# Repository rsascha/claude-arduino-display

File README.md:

# CrowPanel ESP32 5.79" E-Paper HMI Display

Setup für das Elecrow CrowPanel ESP32 5.79" E-Paper HMI Display (272×792, S/W, SPI).

## Hardware

| | |
|---|---|
| MCU | ESP32-S3-WROOM-1-N8R8 (8 MB Flash, 8 MB OPI-PSRAM, 240 MHz) |
| Display | 5.79", 272×792, Schwarz/Weiß |
| Display-Controller | 2× SSD1683 (zwei Panel-Hälften) |
| USB-UART | CH340 (VID 0x1A86 / PID 0x7523) |
| Port | `/dev/cu.usbserial-210` |
| Akku-Anschluss | SH1.0, 2-polig (1,0 mm Raster), 3,7 V Li-Ion, Ladeschaltung an Bord |

**Der BAT-Stecker ist SH1.0, nicht 1,25 mm.** Ein JST/MX1.25-Akku passt nicht ohne
Adapter. Und: Handelsübliche SH1.0-Akkukabel haben teils vertauschte Polung — vor dem
ersten Anstecken gegen den Aufdruck + / − am Stecker messen. Belege und Quellen in
`material/CLAUDE.md` → *Akkuanschluss*; das Benutzerhandbuch schreibt an der Stelle
nur „BAT" und nennt den Typ nicht.

## Board-Einstellungen (Arduino IDE)

`Werkzeuge` →

| Einstellung | Wert |
|---|---|
| Board | **ESP32S3 Dev Module** |
| Flash Size | **8MB (64Mb)** |
| Partition Scheme | **Huge APP (3MB No OTA/1MB SPIFFS)** |
| PSRAM | **OPI PSRAM** |
| CPU Frequency | 240MHz (WiFi) |
| Flash Mode | QIO 80MHz |
| USB CDC On Boot | Disabled |
| Upload Mode | UART0 / Hardware CDC |
| Upload Speed | **460800** — 921600 scheitert beim CH340 mit "Unable to verify flash chip connection" |
| Port | `/dev/cu.usbserial-210` |

Als FQBN für die CLI:

```
esp32:esp32:esp32s3:FlashSize=8M,PartitionScheme=huge_app,PSRAM=opi,CPUFreq=240,FlashMode=qio,UploadSpeed=460800
```

## Pinbelegung E-Paper

Maßgeblich ist `spi.h` in den Beispielen — **nicht** `DEV_Config.h` aus der `EPD`-Library
(die enthält die Waveshare-Standardpins und passt nicht zu diesem Board).

| Signal | GPIO |
|---|---|
| SCK | 12 |
| MOSI | 11 |
| RES (Reset) | 47 |
| DC | 46 |
| CS | 45 |
| BUSY | 48 |
| Display-Power-Enable | 7 (muss in `setup()` auf HIGH!) |

Ohne `digitalWrite(7, HIGH)` bleibt das Panel stromlos und zeigt nichts an.

## Bedienelemente

Laut Benutzerhandbuch (`material/crowpanel-5.79-benutzerhandbuch.pdf`, S. 2–3) hat das
Board fünf Bedienelemente. Drei davon sitzen an der Gehäusekante und sind frei
programmierbar, zwei liegen auf der Platine und sind fest verdrahtet:

| Element | Lage | Funktion |
|---|---|---|
| MENU | Kante | frei programmierbar |
| Rotary Switch (Drehschalter) | Kante | frei programmierbar, dreh- **und** drückbar |
| EXIT | Kante | frei programmierbar |
| BOOT | Platine | hält GPIO 0 auf LOW → Flash-Modus |
| RESET | Platine | zieht EN auf LOW → Neustart |

Das Handbuch nennt keine GPIOs. Sie stehen in `examples/5.79_key`; die Zuordnung wurde
am 23.08.2026 **am Gerät verifiziert** — jedes Element einzeln betätigt und der Zähler
auf dem Panel abgelesen. Die Positionsangaben gelten für die Ausrichtung **Querformat,
USB-Anschluss oben, Bedienelemente an der linken Kante**:

| Position | Element | GPIO | `#define` in `5.79_key` |
|---|---|---|---|
| oben | EXIT | 1 | `EXIT_KEY` |
| Mitte, Rad nach oben | Drehschalter | 4 | `NEXT_KEY` |
| Mitte, Rad drücken | Drehschalter | 5 | `OK_KEY` |
| Mitte, Rad nach unten | Drehschalter | 6 | `PRV_KEY` |
| unten | MENU | 2 | `HOME_KEY` |

Die Reihenfolge an der Kante ist damit **EXIT – Drehschalter – MENU**. Das Handbuch (S. 2)
zeigt sie umgekehrt, weil seine Abbildung die **Rückseite** mit USB-C unten darstellt —
gedreht auf die obige Ausrichtung kehrt sich die Reihenfolge um.

Nachvollziehen lässt sich das mit `make flash SKETCH=examples/5.79_key`: Jeder Tastendruck
schreibt seinen Namen auf Display und Konsole. Zwei Dinge sind an der Elecrow-Vorlage
angepasst — ein Textrest `Reset Tag` mitten im Code, der das Kompilieren verhinderte,
und `Paint_NewImage(..., 0, ...)` statt `Rotation` (180), damit das Bild bei USB oben
richtig herum steht.

Die Taster liegen gegen Masse und werden mit `pinMode(pin, INPUT)` gelesen;
gedrückt ist **LOW**. GPIO 41 schaltet die Power-LED (`examples/5.79_PWR`).

## Verwendung

```bash
make build                              # Standard-Sketch kompilieren
make flash                              # kompilieren + flashen
make monitor                            # serieller Monitor (115200)
make port                               # erkannten Port anzeigen

make flash SKETCH=examples/5.79_wifi    # anderen Sketch wählen
```

## Struktur

```
sketches/         Eigene Sketches — siehe Abschnitt „Sketches"
libraries/        Elecrow-Libraries — zugleich Sketchbook-libraries/
examples/         Offizielle Elecrow-Beispiele + Demos
factory_firmware/ Werksfirmware als Backup
material/         Handbuch + Datenblätter (PDF und .txt), Fotos des laufenden Panels,
                  Kommando- und GPIO-Tabellen als YAML
tools/simulator/  Host-Build eines Sketches -> PNG, ohne Gerät
Makefile          Build-/Flash-Targets, dazu `make sim` und `make material-txt`
LICENSE           MIT für den eigenen Code, plus Herkunft des Fremdmaterials
```

Ein Sketch-Ordner und die `.ino` darin müssen **gleich heißen**
(`sketches/hello_epaper/hello_epaper.ino`). Alle weiteren Dateien im Ordner
werden automatisch mitkompiliert — deshalb liegen `EPD.cpp`, `spi.cpp` &
Co. direkt neben der `.ino` und nicht in `libraries/`.

`src/` wäre als Ordnername ungeeignet: Arduino behandelt ein `src/`
*innerhalb* eines Sketches als Sonderfall (wird als einziger Unterordner
rekursiv kompiliert). Im Sketchbook-Wurzelverzeichnis sind zudem
`libraries/` und `hardware/` fest vergeben.

Der Sketchbook-Pfad von Arduino IDE **und** arduino-cli zeigt auf dieses
Verzeichnis, damit `libraries/`, `examples/` und `sketches/` automatisch gefunden werden.
Rückgängig: in der IDE unter `Einstellungen → Sketchbook-Speicherort`, für die CLI
mit `arduino-cli config set directories.user ~/Documents/Arduino`.

## Sketches

Eigene Sketches in `sketches/`. Kompilieren und flashen mit
`make flash SKETCH=sketches/<name>`.

| Sketch | Kurz | WLAN |
|---|---|---|
| [`hello_epaper`](sketches/hello_epaper) | Text, Formen, Grundlayout — der Einstieg | – |
| [`smiley`](sketches/smiley) | eigene Bogen-Funktion, `safePixel()`, Kreise mit Strichstärke | – |
| [`ha_temperatur`](sketches/ha_temperatur) | ein Sensorwert aus Home Assistant, groß auf dem Display | ja |
| [`ha_verlauf`](sketches/ha_verlauf) | Temperaturkurve über 10 Tage mit Gitter und Achsen | ja |
| [`ha_raeume`](sketches/ha_raeume) | sechs Räume plus Außen in einem Diagramm | ja |
| [`ha_kacheln`](sketches/ha_kacheln) | alle Räume plus Außen als Kacheln, sortiert nach Temperatur | ja |
| [`ha_wetter`](sketches/ha_wetter) | Wind, Luftdruck und Wetterlage in vier Spalten | ja |
| [`ha_wechsel`](sketches/ha_wechsel) | Temperaturen und Wetter im Wechsel, EXIT und MENU bedienbar | ja |
| [`ha_umschalten`](sketches/ha_umschalten) | zwei Sensoren im Wechsel; Testsketch für die Refresh-Modi | ja |
| [`progress_bar`](sketches/progress_bar) | Fortschrittsanzeige, EXIT startet neu — Partial-Refresh | – |
| [`bedienleiste`](sketches/bedienleiste) | Laschen für die drei Bedienelemente, daneben vier umschaltbare Seiten | – |

**`hello_epaper`** — der Startpunkt. Text in mehreren Größen, ein Rahmen, ein paar Formen.
Zeigt, warum der Puffer 27200 Byte groß ist und was `digitalWrite(7, HIGH)` damit zu tun
hat, dass überhaupt etwas erscheint.

**`smiley`** — ergänzt fehlende Zeichenprimitive. `EPD.h` kann Linie, Rechteck und Kreis,
aber **keinen Bogen**; der Mund wird deshalb aus einzelnen Pixeln gebaut (Schrittweite
`0.5f / radius`, sonst reißt die Linie bei großen Radien auf). Hier steht auch der
`safePixel()`-Wrapper, den jeder eigene Zeichencode braucht: `Paint_SetPixel()` prüft seine
Koordinaten nicht und schreibt sonst über den Puffer hinaus.

**`ha_temperatur`** — ein Wert aus Home Assistant über `GET /api/states/<entity_id>`, groß
dargestellt. Fehler landen **auf dem Display**, nicht nur im Log: HTTP 401 und 404 werden
mit einem Hinweis auf die wahrscheinliche Ursache angezeigt, sonst sieht man bei einem
Problem nur ein leeres Panel.

**`ha_verlauf`** — Aktualisierung alle 30 Minuten.
Holt 10 Tage History und zeichnet daraus eine Kurve mit Gitter, Datums- und Gradachse. Die
Antwort (~19 KB) wird direkt mit `strstr()` gescannt statt mit einem JSON-Parser, und je
Pixelspalte wird ein Wert gehalten — der Speicherbedarf bleibt so konstant, egal wie viele
Messpunkte zurückkommen. Warum es 10 und nicht 14 Tage sind, steht unter
*Home Assistant* → `purge_keep_days`.

**`ha_raeume`** — sechs Temperaturkurven in einem Diagramm: Wohnzimmer, Schlafzimmer,
Badezimmer, Küche, Flur und Außen. Zeigt die zwei Probleme, die dabei auftreten und die es
bei einer einzelnen Kurve nicht gibt:

*Keine Farben.* Sechs verschiedene Strichmuster waren der erste Versuch, wirkten auf dem
Panel aber unruhig. Jetzt sind alle Kurven durchgezogen und werden rechts neben ihrem
Endpunkt beschriftet. Weil die Kurven dort oft nur wenige Pixel auseinanderliegen — aktuell
enden alle sechs zwischen 21,6 und 22,9 °C, also innerhalb von zehn Pixeln — weichen
kollidierende Beschriftungen nach unten aus, und eine Führungslinie verbindet jede mit
ihrem tatsächlichen Kurvenende. Ohne die ginge durch das Verschieben genau die Zuordnung
verloren, um die es geht. Der Preis: Wo sich zwei Kurven kreuzen, lässt sich nicht mehr
sagen, welche welche ist.

*Gemeinsame y-Achse.* Außen (der Solarnode) erreicht in der Sonne knapp 40 °C, innen liegt
alles zwischen 20 und 28. Die Achse umfasst deshalb rund 20 K, und die fünf Innenkurven
drängen sich im unteren Drittel. Das ist bewusst so: Eine gekappte Außenkurve würde zeigen,
*dass* es draußen wärmer war, aber nicht wie warm — und genau dieser Kontrast ist der
interessante Teil.

Fällt ein Sensor aus, zeichnet der Sketch die übrigen und markiert den fehlenden in der
Legende mit `n/a`. Nur wenn alle sechs ausfallen, erscheint ein Fehlerbild — anders als
`ha_verlauf`, wo eine fehlende Antwort das ganze Bild kostet.

**`ha_kacheln`** — dieselben sechs Sensoren wie `ha_raeume`, aber ohne Verlauf: ein
3×2-Raster aus Kacheln mit Name, aktuellem Wert in Schriftgröße 48 und dem Trend gegenüber
dem Stand von vor drei Stunden. Sortiert ist nach Temperatur, warm nach kalt in
Lesereihenfolge — oben links der wärmste Raum, unten rechts der kälteste. Die Rangfolge
steckt damit in der Anordnung und braucht keine eigene Beschriftung.

*Trend neben den Wert, nicht darunter.* Als dritte Textzeile kostete er 30 px Höhe; neben
dem Wert kostet er nichts, weil dort ohnehin 94 px frei sind. Die gewonnene Höhe geht an
Name und Trend, die dadurch von Größe 16 auf 24 wachsen konnten — der Messwert selbst nicht,
48 ist die größte Größe, die `EPD_ShowChar()` kennt. Der Trend steht rechtsbündig an der
Kachelkante statt in festem Abstand hinter dem Wert: „23,1" und „-3,5" sind verschieden
breit, ein mitwandernder Trend ließe die sechs Kacheln unruhig wirken.

*Warum drei Stunden.* Die SONOFF-Sensoren lösen 0,1 K auf. Über eine Stunde bewegt sich ein
geschlossener Raum oft nur um genau diesen einen Schritt — der Pfeil zeigte dann Rauschen
an. Über drei Stunden ist ein geöffnetes Fenster deutlich zu sehen, der Tagesgang draußen
aber noch nicht beherrschend. Als unverändert gilt alles unter 0,2 K; dafür gibt es einen
waagerechten Strich statt eines Pfeils.

*Eine Abfrage statt zwei.* Der Trend kommt aus derselben History-Antwort wie der aktuelle
Wert: letzter Messwert der Antwort = jetzt, letzter Messwert vor dem Referenzzeitpunkt =
Vergleich. Ein zusätzliches `GET /api/states/<entity_id>` wäre eine zweite Anfrage für eine
Zahl, die schon da ist. Gesucht wird dabei bewusst der letzte Wert **vor** dem
Referenzzeitpunkt und nicht der erste der Antwort — nur so liefert die Funktion auch dann
den richtigen Vergleich, wenn ihr ein längerer Zeitraum vorgesetzt wird, wie es der
Simulator mit seinen 10-Tage-Dateien tut.

*Zahlen auf Deutsch.* `snprintf()` schreibt immer einen Punkt, und die Locale-Umschaltung,
die das ändern würde, gibt es in der Arduino-Laufzeit nicht — das Komma wird deshalb
nachträglich gesetzt. Damit fällt sofort auf, dass der Font dickte-gleich ist: Das Komma
bekommt dieselbe Zellenbreite wie eine Ziffer, seine Tinte belegt davon aber nur die ersten
7 von 24 px. „23,1" sah dadurch aus, als stünde dort ein Leerzeichen. Der Wert wird deshalb
zeichenweise gesetzt und nach dem Komma nur um `size/4` vorgerückt — weiter nicht, denn
`EPD_ShowChar()` malt die ganze Zelle inklusive Hintergrund und würde das Komma sonst
wieder ausradieren. Die Trendzahl steht bewusst **ohne** Einheit da: korrekt wäre Kelvin,
weil es eine Differenz ist, aber ein „K“ hinter der Zahl fragt auf einem Wohnzimmer-Display
mehr, als es beantwortet. Was gemeint ist, sagen der Pfeil und die Fußzeile.

*Pfeil selbst gezeichnet.* Die Font-Arrays decken ASCII 32..126 ab, ein Pfeilzeichen ist
nicht dabei. Das Dreieck wird deshalb zeilenweise gefüllt statt als Umriss: bei 16 × 12 px
wäre eine 1 px starke Kontur auf dem Panel kaum zu erkennen — dieselbe Beobachtung wie bei
`EPD_DrawCircle()`. Aus dem gleichen Grund sind Rahmen und Rasterlinien 2 px stark.

*Refresh.* Alle 10 Minuten `EPD_FastUpdate()`, jeder sechste Durchgang — also stündlich —
mit Löschzyklus. Genau die Aufteilung, die der Vergleich in `ha_umschalten` nahelegt:
Fast-Update als Regelfall, Vollrefresh nur, um Ghosting einzusammeln. `ha_verlauf` macht
das noch anders und fährt bei jeder Aktualisierung den vollen Zyklus.

Fällt ein Sensor aus, zeigt seine Kachel `n/a` und rutscht ans Ende der Sortierung; ein
Fehlerbild gibt es nur, wenn alle sechs ausfallen.

**`ha_wetter`** — vier Spalten: Kompassrose mit Pfeil, Windgeschwindigkeit, Luftdruck mit
der Änderung der letzten drei Stunden, Wetter-Icon. Der Sketch, an dem am meisten selbst
gezeichnet wird — `EPD.h` kennt Linie, Rechteck und Kreis, sonst nichts.

*Der Pfeil zeigt, woher der Wind kommt.* Home Assistant liefert die Windrichtung nach
meteorologischer Konvention als Herkunft: 341° heißt „aus NNW". Ein kartenüblicher Pfeil in
Wehrichtung zeigte damit nach SSO, während daneben „NNW" steht — Bild und Text sähen aus,
als widersprächen sie sich. Deshalb zeigt der Pfeil auf die NNW-Marke der Rose, und Rose,
Pfeil und Text sagen dasselbe.

*Luftdruck vom Solarnode, nicht aus der Vorhersage.* Beide Quellen sind da und 16 hPa
auseinander: `weather.forecast_home` meldet 1024 hPa auf Meereshöhe reduziert, der
Solarnode misst 1008 hPa vor Ort. Für die Aussage ist das ohne Belang — beim Luftdruck
zählt die Tendenz, und eine Differenz ist höhenunabhängig. Die drei Stunden sind nicht
willkürlich, sondern der meteorologische Standardzeitraum für die Drucktendenz.

*Icons als Umriss über den Umweg Weiß.* Eine flächig schwarze Wolke wäre auf E-Paper ein
Klecks. Ein Umriss aus einzelnen Bögen scheitert daran, dass sich die Bögen der drei
Wolkenbäuche gegenseitig durchschneiden. Der Ausweg: die ganze Form zweimal zeichnen —
erst 2 px größer in Schwarz, dann in Weiß darüber. Übrig bleibt ein sauberer Umriss, und
weil die weiße Füllung alles darunter löscht, verdeckt die Wolke beim Icon *heiter*
automatisch die Sonnenstrahlen hinter ihr.

*Fünf Icons plus Mond.* Home Assistant kennt 15 Wetterzustände. Mit nur Sonne und Regen
wären `cloudy` und `fog` als Sonnentag durchgegangen. Was nicht in der Zuordnungstabelle
steht, wird zur Wolke mit dem Rohzustand als Text — besser ein unbekanntes Wort als ein
falsches Bild. Getestet sind alle sechs Bilder, indem dem Simulator nacheinander jeder
Zustand untergeschoben wurde; auf Schnee oder Mond hätte man sonst bis zum Winter oder bis
zur Nacht warten müssen.

**`ha_wechsel`** — die beiden vorigen Sketches in einem: alle 60 Sekunden wechselt das
Bild zwischen den Temperaturkacheln und der Wetterseite. **EXIT** (GPIO 1) blättert sofort
um und startet die Minute von vorn, damit die aufgerufene Seite in Ruhe lesbar bleibt.
**MENU** (GPIO 2) holt die Daten neu und zeichnet die aktuelle Seite frisch.

*Daten getrennt vom Bildwechsel.* Geholt wird alle zehn Minuten, gezeichnet aus dem
Zwischenspeicher. Andernfalls liefe jede Minute eine Runde von elf HTTP-Anfragen, und beim
Umblättern sähe man die Netzwerklatenz statt das Panel — dieselbe Trennung wie in
`ha_umschalten`. Läuft der Zehn-Minuten-Abruf ab, wird **nicht** neu gezeichnet: der
nächste Wechsel steht ohnehin binnen einer Minute an und bringt die frischen Zahlen mit.
Ein zusätzlicher Bildaufbau wäre ein Refresh-Zyklus für nichts.

*Aufgeteilt auf mehrere Dateien.* `draw.cpp` hält die Zeichenhilfen, `screen_temperaturen.cpp`
und `screen_wetter.cpp` je eine Seite, die `.ino` nur Daten, Tasten und Taktung. In einer
einzigen `.ino` wären es rund 900 Zeilen mit der Hälfte doppelt — beide Seiten brauchen
dieselben Primitive, weil `EPD.h` nur Linie, Rechteck und Kreis kennt. Der Simulator
übersetzt seitdem alle `.cpp` des Sketch-Ordners (siehe `SIM_SRCS` im `Makefile`) statt nur
`EPD.cpp`.

*Fußzeile mit Platzprüfung.* Der Tastenhinweis sitzt mittig in der tatsächlich freien Lücke
zwischen Zeitstempel und rechtem Text, nicht auf der Bildmitte: die rechten Texte sind je
Seite verschieden lang, und auf der Temperaturseite stand sonst
„EXIT blaetPfeil und Zahl:" übereinander. Passt der Hinweis nicht, entfällt er ganz.

*Ein Wechsel pro Minute sind 1.440 Bildwechsel am Tag.* Deshalb Fast-Update als Regelfall
und nur jeder 60. Aufbau — also stündlich — mit Löschzyklus. Bei jedem Wechsel voll zu
refreshen hieße sechzigmal pro Stunde mehrfaches Schwarzblitzen; das fällt mehr auf als
das Ghosting, das es verhindert.

**`ha_umschalten`** — Testsketch. Blendet im 5-Sekunden-Takt zwischen Wohnzimmer- und
Schlafzimmerkurve um und wechselt dabei reihum Voll-, Fast- und Partial-Refresh durch;
Modus und gemessene Dauer stehen auf dem Display. Ergebnis siehe
*Die drei Refresh-Modi*. Beide Verläufe werden einmal geholt und im Speicher gehalten —
löste jedes Umschalten eine HTTP-Anfrage aus, würde der Test die Netzwerklatenz messen
statt das Panel. **Kein Dauerbetrieb:** E-Paper verträgt keine unbegrenzte Zahl an
Refresh-Zyklen.

**`progress_bar`** — fünf Segmente, alle 3 Sekunden eines mehr, EXIT startet neu. Der
Gegentest zu `ha_umschalten`: Partial taugt nichts für einen Vollbildwechsel, wohl aber
hier, wo sich pro Schritt nur ein Segment ändert. Der Sketch zeigt die zwei Bedingungen,
ohne die das nicht funktioniert — `EPD_Clear_R26A6H()` vor dem ersten Partial-Update und
kein Hardware-Reset zwischendurch. Ausführlich in
**[`sketches/progress_bar/CLAUDE.md`](sketches/progress_bar/CLAUDE.md)**.

**`bedienleiste`** — die drei Bedienelemente an der linken Gehäusekante bekommen ein
Gegenstück auf dem Panel: oben eine Lasche mit **E** für EXIT, unten eine mit **M** für
MENU, dazwischen die des Drehschalters. Wer drückt, sieht seine Lasche schwarz werden.
Damit ist ohne Serial-Monitor am Gerät ablesbar, welches Element wo sitzt und welchen GPIO
es zieht.

*Die y-Positionen sind gemessen, nicht gerechnet.* 60–70 für EXIT, 110–150 für den
Drehschalter, 200–210 für MENU. Abgelesen wurden sie mit einem Wegwerf-Sketch, der an
beiden langen Kanten ein Maßband von 0 bis 271 zeichnet — Striche alle 10 px, Beschriftung
alle 50 px. Er hat seinen Zweck erfüllt und ist wieder gelöscht; die Zahlen stehen jetzt
hier und in `CLAUDE.md`. EXIT und MENU liegen
mit ihren Mitten 65 und 205 symmetrisch zur Bildmitte, das hätte man annehmen können. Die
Mitte des Drehschalters liegt aber bei 130 und damit sechs Pixel darüber, und die Höhen der
drei Elemente stehen in keinem Datenblatt. Beides fällt nur beim Messen auf.

*Keine Lasche hat die Höhe ihres Elements.* Sie sitzt auf dessen **Mitte** — das ist die
Information, auf die es beim Zuordnen ankommt; die Höhe richtet sich danach, was
hineinpassen muss. Die beiden Taster sind nur 11 px hoch, ein Buchstabe in Größe 24
braucht 24 px, und kleiner ist auf dem Panel nicht mehr sicher lesbar: also 32 px. Das Rad
ist 41 px hoch, seine Lasche 53 — Pfeil, `OK` und Pfeil brauchen zusammen mehr, wenn sie
Abstand behalten sollen.

*Auf fünf Ebenen aufgeteilt, damit die Leiste woanders verwendbar bleibt.* `zeichnen.cpp`
hält die Primitive, `tasten.cpp` kennt nur GPIOs und Entprellung, `laschen.cpp` nur die
Laschen, `seiten.cpp` nur den Inhaltsbereich, `panel.cpp` bringt den Puffer aufs Display —
die `.ino` verbindet alles. **Der Vertrag zwischen den beiden Zeichenebenen ist eine
Spalte:** Die Laschen fassen nur `x < 46` an, die Seiten nur `x >= 70`, und keine von
beiden ruft `Paint_Clear()`. Das steht genau einmal in `setup()`. Nur so lässt sich der
Inhalt wechseln, ohne die Laschen anzufassen — und nur so wäre die Leiste in einem Sketch
wie `ha_wechsel` brauchbar, der den Rest des Bildes besitzt. Dass EXIT den Vollrefresh
scharf macht, bleibt aus demselben Grund in der `.ino`: In `ha_wechsel` blättert EXIT um.

*Der Vertrag gilt auch auf sechs Pixel genau.* Die Menü-Markierung begann anfangs sechs
Pixel links des gelöschten Bereichs. Diese sechs Pixel wurden nie wieder weiß, und jede
Position, auf der die Markierung stand, ließ dort einen schwarzen Stummel zurück — bis
daraus ein durchgehender Balken über die ganze Liste wurde. Bei einem `Paint_Clear()` wäre
das nie aufgefallen: Wer partiell zeichnet, kauft Geschwindigkeit mit Genauigkeit.

*Der Drehschalter ist kein Encoder — das ist gemessen.* Der Schaltplan nennt einen
Quadratur-Encoder; am Gerät ziehen die beiden Phasen aber nie gleichzeitig, jede Betätigung
ist ein einzelner Impuls von 250–640 ms auf genau einer Leitung. Ein Dekoder hätte nichts
zu dekodieren. Herausgefunden mit einem Mitschnitt ohne Entprellung: Das normale Log war
nicht das Signal, sondern die Ausgabe eines für Taster gebauten Filters — und der zerhackt
die Flankenfolge, bis kein Muster mehr erkennbar ist.

*Drei Funktionen, eine Lasche.* Der Drehschalter ist ein einziges Bedienelement mit drei
Kontakten (GPIO 4 hoch, 5 drücken, 6 runter). Er bekommt deshalb **eine** Lasche, die in
drei Zonen geteilt ist — Pfeil hoch, `OK`, Pfeil runter — und beim Bedienen färbt sich nur
die betroffene Zone. Drei getrennte Laschen hätten drei Bedienelemente vorgetäuscht, wo
nur eines ist. Die Pfeile sind aus Pixeln gefüllt: Die Font-Arrays decken ASCII 32..126 ab,
ein Pfeilzeichen ist nicht dabei.

*Zwischen den drei Zonen liegen 4 px, und das ist ein Bugfix, kein Geschmack.* Zuerst
lagen Pfeil, `OK` und Pfeil ohne Abstand aneinander. Passiv sah das gut aus — invertiert
nicht: Die Zonengrenze lag genau auf der Inhaltskante, und der weiße Pfeil stieß mit seiner
breitesten Zeile an die weiße Fläche daneben. Er las sich dadurch als **Kerbe** im
schwarzen Balken statt als Pfeil, und in der `OK`-Zone wirkten die beiden schwarzen Pfeile
abgeschnitten. Aufgefallen ist das erst, als alle vier Zustände nebeneinander gerendert
wurden — einzeln und in Originalgröße sah jeder für sich plausibel aus. Der Simulator kann
das, ohne zu flashen; der Weg steht in `sketches/bedienleiste/CLAUDE.md`.

*Weiß auf Schwarz kostet nichts.* Für die gedrückte Lasche genügt `EPD_ShowString(...,
WHITE)`. Das funktioniert, weil `EPD_ShowChar()` die ganze Zelle malt und für den
Hintergrund `!color` setzt — bei `WHITE` also Schwarz. Dieselbe Eigenschaft, die in
`ha_kacheln` das Komma ausradiert hat, ist hier genau das Gewünschte.

*Refresh.* Pro Tastendruck zwei Partial-Updates — eines beim Drücken, eines beim
Loslassen. Die Bedingungen dafür stehen in
[`sketches/progress_bar/CLAUDE.md`](sketches/progress_bar/CLAUDE.md):
`EPD_Clear_R26A6H()` vor dem ersten Partial-Update und kein Hardware-Reset zwischendurch.

*Der Vollrefresh läuft auf Zuruf, und zwar in zwei Schritten.* Erst war er alle 20
Teilbilder fällig — und traf damit mitten ins Bedienen: Der Löschzyklus lässt das Panel
mehrere Sekunden **weiß** stehen, und wer gerade draufschaut, hält das für einen Absturz.
Jetzt macht der erste Druck auf **EXIT** aus dem `E` ein `R`, und erst der Druck auf `R`
wischt. Jede andere Taste bricht ab, und nach fünf Sekunden ohne Tastendruck verfällt das
`R` von selbst — ein Bedienelement, das in einem vergessenen Sonderzustand steht, löst beim
nächsten beiläufigen Druck etwas aus, das man nicht wollte.

Das `R` wird dabei **invertiert** gezeichnet und bleibt es, auch wenn die Taste längst
losgelassen ist: Es ist ein Zustand, kein Tastendruck. Nur den Buchstaben zu tauschen war zu
leise — `E` und `R` sind beide schmal, stehen an derselben Stelle und in derselben Größe,
und die Lasche wurde beim Loslassen wieder weiß. Der Wechsel ging im Blick auf das ganze
Panel unter. Zwei Schritte deshalb, weil ein
Bedienelement, das man nur antippen will, um zu sehen ob es reagiert, nicht nebenbei das
halbe Display für Sekunden ausknipsen soll. Gewischt wird dabei das **Ruhebild**, nicht die
gedrückte Lasche — sonst müsste das Loslassen den großen schwarzen Block per Teilrefresh
wieder wegnehmen, und genau das kann Partial am schlechtesten. Wie viele Teilbilder seit
dem letzten Wischen aufgelaufen sind, steht in der Fußzeile.

*Der Neuaufbau nach dem Löschzyklus ist am Gerät ermittelt, nicht hergeleitet.* Drei
Anläufe, drei verschiedene Fehlerbilder: einmal blieb das Panel komplett weiß, einmal kam
das Bild blass, einmal fehlten Teile des Textes. Der Grund ist, dass RAM `0x26`/`0xA6` im
Datenblatt „Write RAM (RED)" heißt, im Elecrow-Treiber aber als *vorheriges Bild* für den
Teilrefresh dient — und nirgends steht, was davon bei einem vollen Update gilt. Statt weiter
zu raten wurden fünf Rezepte nacheinander auf das Panel geschickt und angesehen, wie es
`ha_umschalten` schon für die drei Refresh-Modi gemacht hat:

| Neuaufbau | ohne `EPD_Clear_R26A6H()` | mit `EPD_Clear_R26A6H()` |
|---|---|---|
| `EPD_Update()` (0xF7) | Text unvollständig | sauber, flackert |
| `EPD_FastUpdate()` (0xC7) | **sauber, kein Flackern** | Panel bleibt weiß |

Die beiden Zutaten müssen also über Kreuz zusammenpassen. Gewählt ist die ruhige
Kombination — das Flackern übernimmt der Löschzyklus davor, der Neuaufbau muss es nicht
wiederholen. Sie entspricht zugleich Elecrows eigenem `5.79_Global_refresh`.

*Und danach muss der Controller erfahren, was er anzeigt.* Auch mit dem richtigen Rezept
kam der **erste** Tastendruck nach einem Wisch nur grau heraus, egal welche Taste; ab dem
zweiten stimmte es. Auf dem Panel stand das Ruhebild, in RAM `0x26`/`0xA6` — dem
„vorherigen Bild", aus dem der Teilrefresh seine Waveform je Pixel wählt — aber noch der
Rest des Löschzyklus. `EPD_Clear_R26A6H()` löst das nicht: Es setzt „vorher alles weiß",
richtig nur direkt nach dem Löschen. Gebraucht wird „genau das, was zu sehen ist", und
dafür gibt es im Treiber keine Funktion. `merkeAltesBild()` schreibt deshalb den Bildpuffer
mit der Adressrechnung aus `EPD_Display()` nach `0x26`/`0xA6`.

Das beantwortet zugleich die Frage, die drei Fehlversuche offengelassen hatten: `0x26`
benutzt **dieselbe Kodierung wie `0x24`**, 1 = weiß. Der Puffer wird unverändert übernommen
und ergibt den richtigen Übergang — der Datenblattname „Write RAM (RED)" führt in die Irre.
Ausführlich in [`sketches/progress_bar/CLAUDE.md`](sketches/progress_bar/CLAUDE.md).

*`INPUT` genügt.* Die fünf Tasten haben 4,7-kΩ-Pull-ups auf der Platine
(`material/SCHALTPLAN.md` → *Tasten*), der Pin ist also nicht offen. `INPUT_PULLUP` würde
nichts verbessern; entprellt wird trotzdem, mit zwei Messungen im Abstand von 15 ms.

Sketches mit WLAN brauchen eine `secrets.h` neben der `.ino`:

```bash
cp sketches/<name>/secrets.h.example sketches/<name>/secrets.h
```

Sie ist per `.gitignore` ausgeschlossen und wird **nicht** committet — committet wird nur
`secrets.h.example` mit Platzhaltern.

## Simulator

Layout ausprobieren, ohne zu flashen:

```bash
make sim-fetch SKETCH=sketches/ha_raeume   # echte HA-Antworten nach tools/simulator/data/
make sim       SKETCH=sketches/ha_raeume   # -> tools/simulator/out.png
```

Der Sketch wird dabei **nativ auf dem Mac** übersetzt und sein Bildpuffer als PNG
ausgegeben. Entscheidend für die Aussagekraft: `EPD.cpp` und `EPDfont.h` sind die *echten*
Dateien aus dem Sketch-Ordner, der Sketch selbst bleibt unverändert. Ersetzt sind nur
Arduino, WLAN und HTTP (`tools/simulator/arduino/`). Der `HTTPClient`-Stub liefert dort, wo
auf dem Gerät die HTTP-Antwort käme, eine lokale Datei — `fetch.sh` holt sie per `curl` aus
der echten Instanz und liest die entity_ids dafür aus der `.ino`, damit keine zweite Liste
veralten kann.

Auch die 8 Pixel Naht bei x = 396 rechnet der Simulator heraus: Das PNG zeigt die
sichtbaren 792 Pixel, nicht den 800 Pixel breiten Rohpuffer.

**Warum dieser Aufwand statt eines schnellen Nachbaus:** Ein Prototyp mit eigenen
Schriftmetriken hat in `ha_verlauf` eine 6-px-Überlappung *nicht* gezeigt, die auf dem Panel
da war. Ein Simulator ist nur so viel wert wie seine Übereinstimmung mit dem Original.
Gleich der erste Lauf hat sich bezahlt gemacht: In der Kopfzeile von `ha_raeume` stand
„Stand 23.08. 16:05 °C" — das Gradzeichen aus `ha_verlauf`, wo es hinter einem Messwert
saß, hing hier hinter der Uhrzeit.

Braucht ImageMagick (`brew install imagemagick`) für die Umwandlung von PBM nach PNG.

## Elecrow-Beispiele

Vorlagen zum Kopieren, in `examples/`.

| Sketch | Inhalt |
|---|---|
| `5.79_Global_refresh` | Vollbild-Refresh, Bild anzeigen |
| `5.79_partial_refresh` | Partielles Update (schnell, ohne Flackern) |
| `5.79_GPIO` | GPIO-Grundlagen |
| `5.79_key` | Tasten-Eingabe |
| `5.79_PWR` | Deep Sleep / Stromsparen |
| `5.79_TF` | SD-Karte |
| `5.79_wifi`, `5.79_wifi_http` | WLAN, HTTP |
| `5.79_BLE` | Bluetooth LE |
| `Demos/` | Openweather-Demo, BLE-/WiFi-Refresh |

## Quellen

- [Elecrow Wiki – 5.79" HMI Display](https://www.elecrow.com/wiki/CrowPanel_ESP32_E-paper_5.79-inch_HMI_Display.html)
- [Elecrow Wiki – Arduino Tutorial](https://www.elecrow.com/wiki/CrowPanel_ESP32_E-Paper_5.79inch_Arduino_Tutorial.html)
- [GitHub – Elecrow-RD/CrowPanel-ESP32-5.79-E-paper-HMI-Display-with-272-792](https://github.com/Elecrow-RD/CrowPanel-ESP32-5.79-E-paper-HMI-Display-with-272-792)
- [Elecrow Forum – DIS08792E mit externem Akku betreiben](https://forum.elecrow.com/discussion/1063/dis08792e-crowpanel-esp32-5-79-e-paper-hmi-display-powering-with-an-external-battery) — SH1.0 statt 1,25 mm, Hinweis auf vertauschte Polung
- Benutzerhandbuch (deutsch): `material/crowpanel-5.79-benutzerhandbuch.pdf` — Rückseiten-Beschriftung, Bedienelemente, Spezifikation
- [SSD1683 Datenblatt](https://www.elecrow.com/download/product/DIS08792E/SSD1683_Datasheet.PDF) — Display-Controller, 49 Seiten; liegt auch als `material/ssd1683-datasheet.pdf` im Repo
- [ESP32-S3-WROOM-1 Datenblatt](https://www.elecrow.com/download/product/DIS08792E/esp32-s3-wroom-1_datasheet.pdf) — Modul, Pinout, elektrische Werte; liegt auch als `material/esp32-s3-wroom-1-datasheet.pdf` im Repo

Die beiden Datenblatt-Links stehen im Handbuch nur als QR-Code (S. 4–5); der Text des
PDFs enthält sie nicht. Deshalb liegen die Datenblätter mit im Repo — geht der Elecrow-
Download irgendwann offline, wäre der Weg dorthin sonst nur noch über die QR-Codes.

## Zeichen-API (Elecrow `EPD.h`)

GxEPD2 liegt zwar in `libraries/`, hat aber **keine Panel-Klasse für 272×792**
(129 Display-Klassen geprüft, SSD1683 nur in 4,2"-Varianten). Für dieses Display
werden daher Elecrows `EPD.cpp`/`spi.cpp` direkt im Sketch-Ordner verwendet.

```c
Paint_NewImage(ImageBW, EPD_W, EPD_H, Rotation, WHITE);  // Puffer anlegen
Paint_Clear(WHITE);

EPD_ShowString(x, y, "Text", size, BLACK);   // size: nur 8, 12, 16, 24, 48
EPD_ShowNum(x, y, wert, stellen, size, BLACK);
EPD_DrawLine(x1, y1, x2, y2, BLACK);
EPD_DrawRectangle(x1, y1, x2, y2, BLACK, mode);   // mode 0 = Umriss, 1 = gefüllt
EPD_DrawCircle(cx, cy, r, BLACK, mode);
EPD_ShowPicture(x, y, w, h, bitmap, WHITE);

EPD_Display(ImageBW);   // Puffer übertragen
EPD_FastUpdate();       // sichtbar machen
EPD_DeepSleep();        // Bild bleibt auch ohne Strom stehen
```

Stolperfallen:

- **`digitalWrite(7, HIGH)` in `setup()`** schaltet die Panel-Spannung. Fehlt das, bleibt das Display dunkel.
- **`EPD_W` ist 800**, sichtbar sind aber nur **792** Pixel. Grund: zwei SSD1683-Controller
  mit je einer Panel-Hälfte, dazwischen 8 ungenutzte Pixel im Speicher. `Paint_SetPixel()`
  korrigiert das selbst (`if (Xpoint >= 396) Xpoint += 8`), gültige x-Werte sind also 0..791.
- **Ausrichtung:** `EPD.h` definiert `Rotation 180` — damit steht das Bild bei diesem
  Aufbau auf dem Kopf. In `hello_epaper.ino` wird stattdessen `DISPLAY_ROTATION = 0`
  an `Paint_NewImage()` übergeben; erlaubt sind 0, 90, 180, 270.
- **Nur die Schriftgrößen 12, 16, 24 und 48 funktionieren.** Alle anderen — **auch 8** —
  zeichnen kommentarlos nichts: `EPD_ShowChar()` hat für 8 zwar eine Größenberechnung,
  aber keinen Zweig zum Font-Array und verlässt die Funktion per `else return;`.
- **Nur ASCII 32..126.** Die Font-Arrays haben 95 Einträge, der Index ist `chr - ' '`.
  Ein `°` (176) ergäbe Index 144 und läse über das Array hinaus — Umlaute ebenso.
  Statt `°C` also `C` schreiben oder den Kreis selbst zeichnen.
- Zeichenbreite ist `size/2` — Text selbst auf Überlauf prüfen, es wird nicht umgebrochen.

### Die drei Refresh-Modi

`EPD_Update()`, `EPD_FastUpdate()` und `EPD_PartUpdate()` unterscheiden sich im Code nur
im Parameter zu Kommando `0x22` (`0xF7`, `0xC7`, `0xDC`; SSD1683-Datenblatt S. 29). Wie
verschieden sie am Panel aussehen, zeigt `sketches/ha_umschalten`, das im 5-Sekunden-Takt
zwischen zwei Kurven umblendet und dabei die Modi durchwechselt. Befund am realen Gerät:

| Modus | Verhalten | wofür |
|---|---|---|
| `EPD_Update()` mit `EPD_Display_Clear()` davor | dauert lange, das Panel wird **mehrfach** komplett schwarz | selten, gegen Ghosting |
| `EPD_FastUpdate()` | schnell und sauber | **Regelfall für Vollbildwechsel** |
| `EPD_PartUpdate()` | für Vollbildwechsel unbrauchbar | nur für kleine Ausschnitte |

Dass Partial hier nichts bringt, hat einen Grund: `EPD_Display()` schreibt immer das
**komplette** RAM beider Controller, ein Fenster gibt es nicht. Der Modus lohnt sich erst,
wenn man vorher den RAM-Adressbereich (`0x44`/`0x45`, S. 34–35) auf den geänderten
Ausschnitt einengt — für eine Fortschrittsanzeige oder eine tickende Uhr also, nicht für
ein neues Vollbild.

Das lange Schwarzwerden von `EPD_Update()` kommt nicht vom Kommando selbst, sondern vom
Löschzyklus davor: erst wird das Panel weiß geschrieben und aktualisiert, dann das Bild.
`ha_verlauf` macht das bei jeder Aktualisierung.

**E-Paper verträgt keine unbegrenzte Zahl an Refresh-Zyklen.** Ein Sketch, der im
Sekundentakt aktualisiert, ist als Test in Ordnung, als Dauerbetrieb nicht.

## Lizenz

Der eigene Code und die Dokumentation stehen unter MIT (siehe `LICENSE`).

`libraries/`, `examples/`, `factory_firmware/` und die PDFs in `material/` sind
Fremdmaterial und behalten die Lizenz ihrer jeweiligen Rechteinhaber — darunter
GPL-3.0 (GxEPD2) und AGPL-3.0 (EPaperDrive). Die Aufstellung steht in `LICENSE`.

Fotos in `material/` werden **ohne EXIF** committet. iPhone-Aufnahmen tragen sonst
GPS-Koordinaten mit ±5 m Genauigkeit; der Umwandlungsbefehl in `CLAUDE.md` entfernt
sie mit `-strip`.

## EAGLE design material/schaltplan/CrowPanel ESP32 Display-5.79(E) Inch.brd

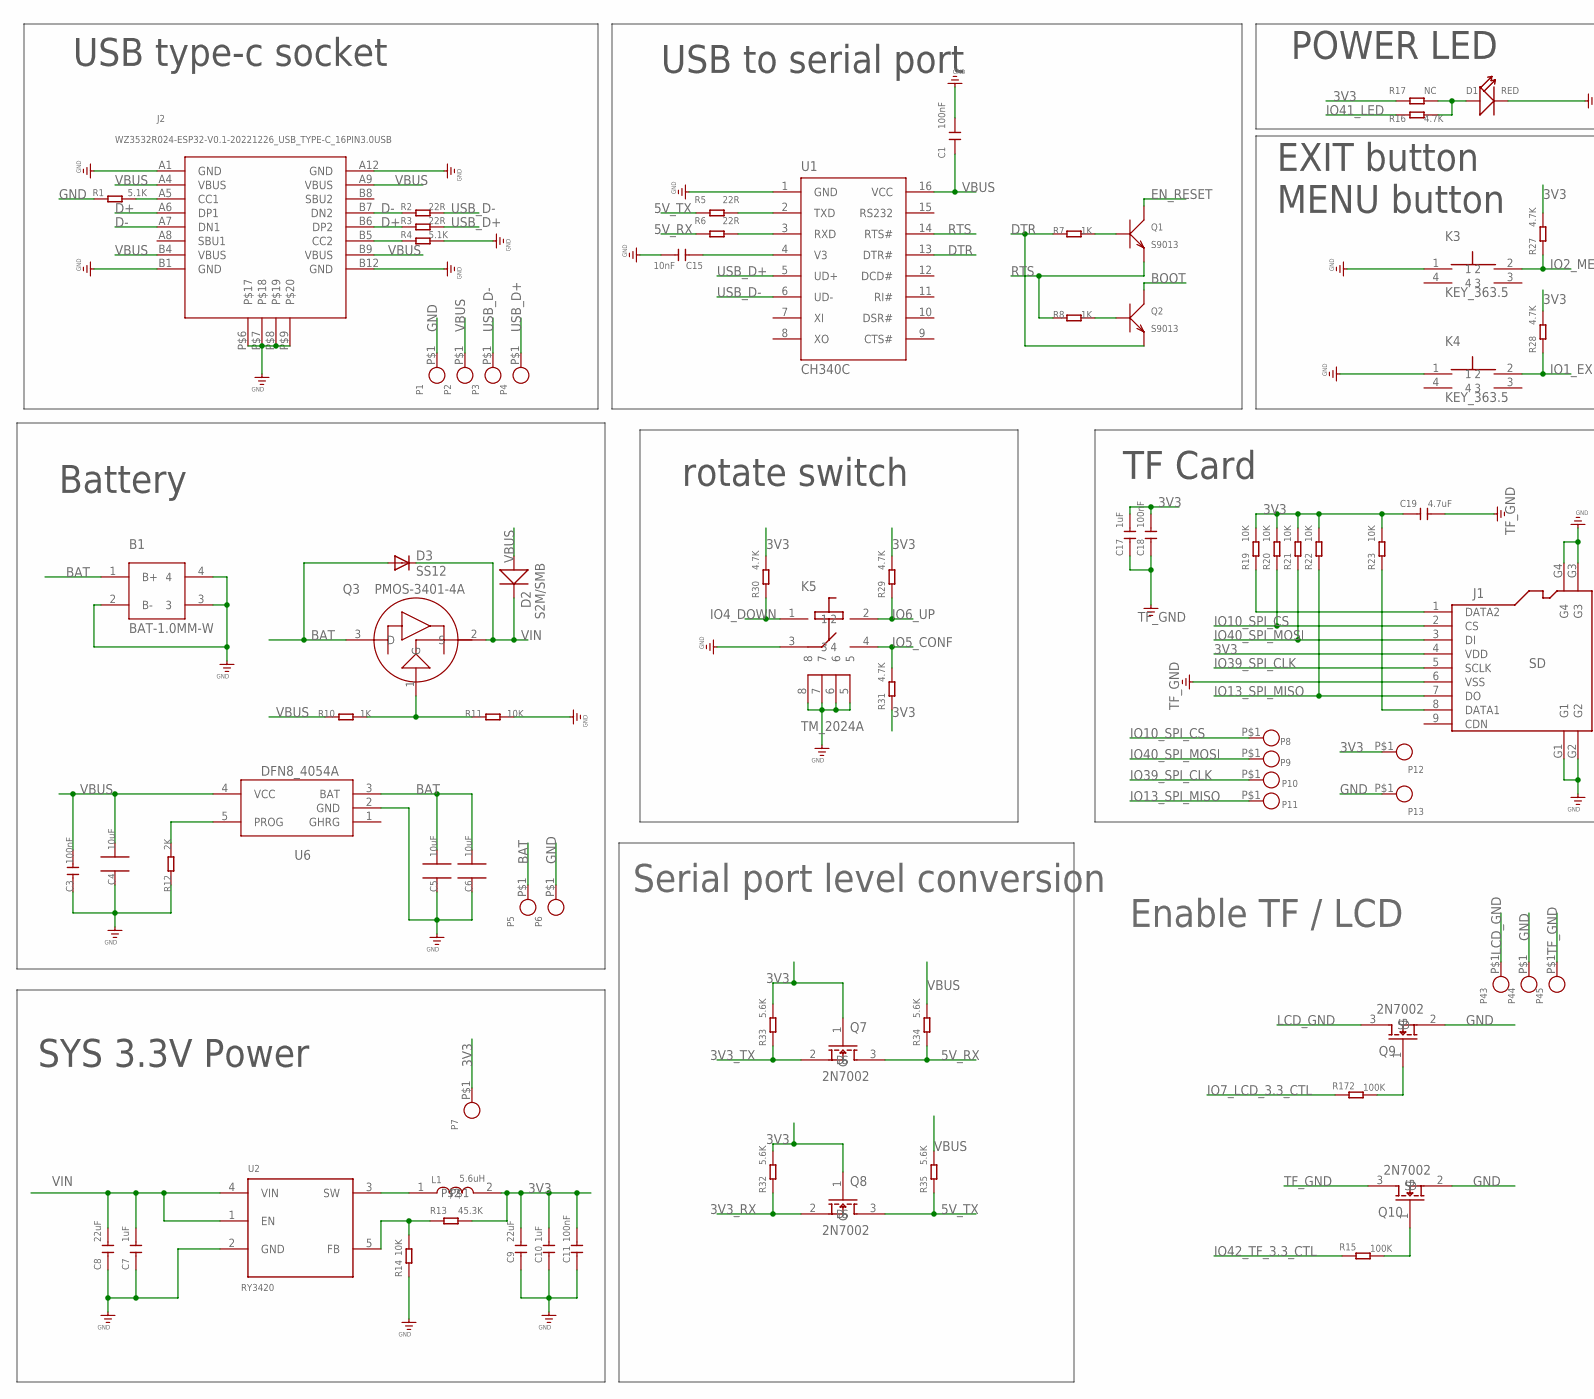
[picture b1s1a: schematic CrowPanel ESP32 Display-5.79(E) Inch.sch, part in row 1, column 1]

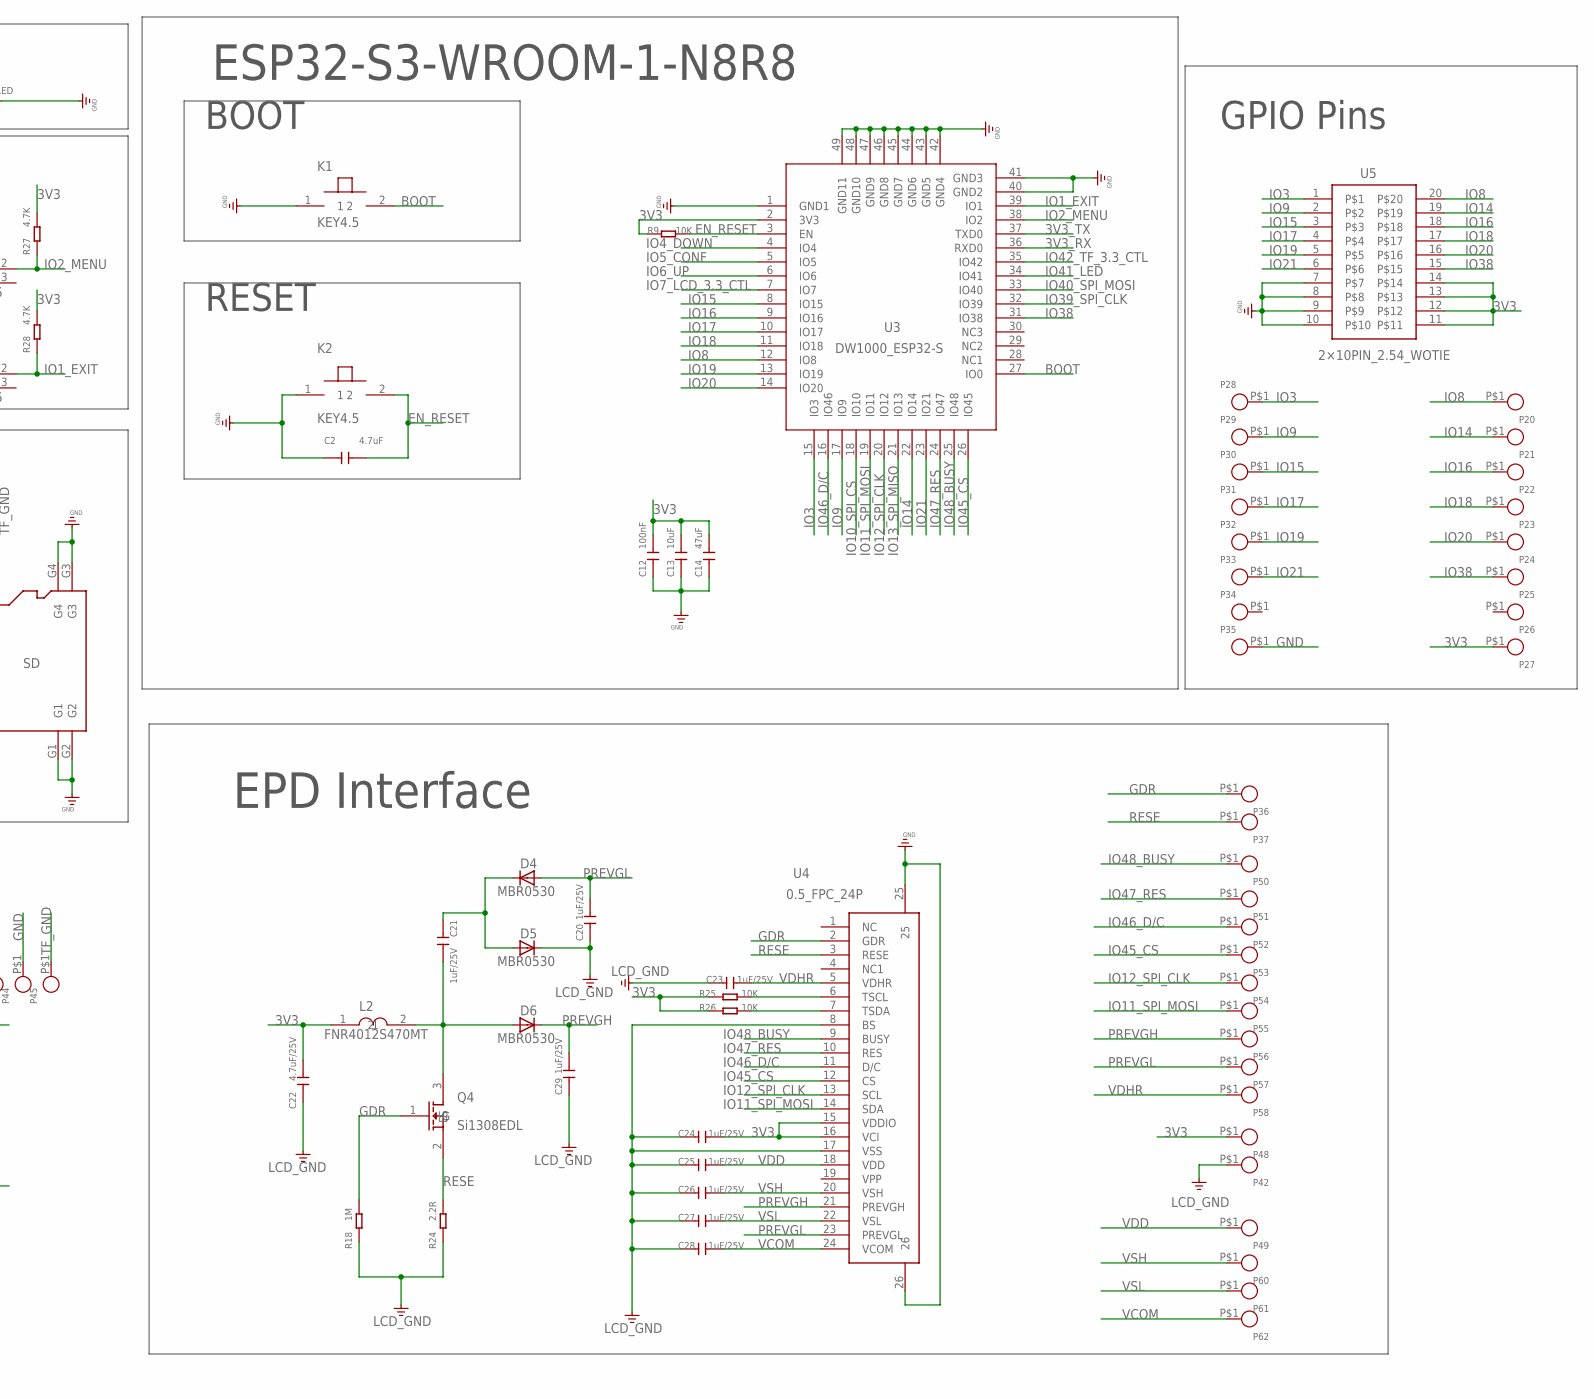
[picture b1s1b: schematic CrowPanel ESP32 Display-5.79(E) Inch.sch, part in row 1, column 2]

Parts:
B1: BAT-1.0MM-W; SH1.0MM-W
C1: 100nF; 0603
C2: 4.7uF; A_XBJ_0603
C3, C12, C18: 100nF; A9G_DISCRETE_C0603
C4, C5, C6: 10uF; CPT_SMD_0805_S
C7, C10: 1uF; A_XBJ_0603
C8, C9: 22uF; A_XBJ_0805
C11: 100nF; A_XBJ_0603
C13: 10uF; A9G_DISCRETE_C0603
C14: 47uF; A9G_DISCRETE_C0805
C15: 10nF; A_XBJ_0603
C17: 1uF; A9G_DISCRETE_C0603
C19: 4.7uF; A9G_DISCRETE_C0603
C20, C21, C23, C24, C25, C26, C27, C28, C29: 1uF/25V; A9G_DISCRETE_C0603
C22: 4.7uF/25V; A9G_DISCRETE_C0603
D1: RED; A_XBJ_DISCRETE_LED-0603
D2: S2M/SMB; DO-214AB_214AB
D3: SS12; DIODE_DO-214AC
D4, D5, D6: MBR0530; DIODE_SOD123
J1: SD; CONNECTOR_9P-SMD-W/-RING
J2: WZ3532R024-ESP32-V0.1-20221226_USB_TYPE-C_16PIN3.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; WZ3532R024-ESP32-V0.1-20221226_KEVIN_3.0TYPEC-SMD
K1, K2: KEY4.5; KEY-4.5
K3, K4: KEY_363.5; KEY_3*6*3.5
K5: TM_2024A
L1: 5.6uH; WZ2432R028-ESP32-V1.2-20231108_CD54_CD54
L2: FNR4012S470MT
P1, P2, P3, P4, P5, P6, P7, P8, P9, P10, P11, P12, P13, P20, P21, P22, P23, P24, P25, P26, P27, P28, P29, P30, P31, P32, P33, P34, P35, P36, P37, P42, P43, P44, P45, P48, P49, P50, P51, P52, P53, P54, P55, P56, P57, P58, P60, P61, P62: CROWPI_POW_PADPAD-1.0MM; CROWPI_POW_PAD-1.0MM
Q1, Q2: S9013; DISCRETE_SOT23$1
Q3: PMOS-3401-4A; DFN8_SOT-23
Q4: Si1308EDL; SOT-323_W
Q7, Q8, Q9, Q10: 2N7002; SOT23-3_W
R1, R4: 5.1K; R0603
R2, R3, R5, R6: 22R; R0603
R7, R8, R10: 1K; A9G_DISCRETE_R0603
R9, R11, R14, R19, R20, R21, R22, R23, R25, R26: 10K; A9G_DISCRETE_R0603
R12: 2K; A9G_DISCRETE_R0603
R13: 45.3K; A9G_DISCRETE_R0603
R15, R172: 100K; R0603
R16, R27, R28, R29, R30, R31: 4.7K; A9G_DISCRETE_R0603
R17: NC; A9G_DISCRETE_R0603
R18: 1M; A9G_DISCRETE_R0603
R24: 2.2R; A9G_DISCRETE_R0603
R32, R33, R34, R35: 5.6K; DISCRETE_R0603
U1: CH340C; A_XBJ_SOP-16
U2: RY3420; CROWBOT_-V1.0-20220525_A_XBJ_SOT23-5
U3: DW1000_ESP32-S; DW1000_ESP32-S3
U4: 0.5_FPC_24P
U5: 2×10PIN_2.54_WOTIE; 2*10PIN_2.54_WOTIE
U6: DFN8_4054A; DFN8_SOP23-5

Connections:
3V3: C9.2, C10.2, C11.2, C12.2, C13.2, C14.2, C17.2, C18.2, C19.2, C22.2, C24.1, J1.4 (VDD), L1.2, L2.1, P7.P$1, P12.P$1, P27.P$1, P48.P$1, Q7.1 (G), Q8.1 (G), R9.1, R13.2, R17.1, R19.2, R20.2, R21.2, R22.2, R23.2, R25.2, R26.2, R27.2, R28.2, R29.2, R30.2, R31.1, R32.2, R33.2, U3.2 (3V3), U4.15 (VDDIO), U4.16 (VCI), U5.11, U5.12, U5.13, U5.14
3V3_RX: Q8.2 (S), R32.1, U3.36 (RXD0)
3V3_TX: Q7.2 (S), R33.1, U3.37 (TXD0)
5V_RX: Q7.3 (D), R6.1, R34.1
5V_TX: Q8.3 (D), R5.1, R35.1
BAT: B1.1 (B+), C5.2, C6.2, D3.A, P5.P$1, Q3.3 (D), U6.3 (BAT)
BOOT: K1.2, Q2.3 (C), U3.27 (IO0)
D+: J2.A6 (DP1), J2.B6 (DP2), R3.1
D-: J2.A7 (DN1), J2.B7 (DN2), R2.1
DTR: Q2.2 (E), R7.1, U1.13 (DTR#)
EN_RESET: C2.2, K2.2, Q1.3 (C), R9.2, U3.3 (EN)
GDR: P36.P$1, Q4.1 (G), R18.2, U4.2 (GDR)
GND: B1.2 (B-), B1.3, B1.4, C1.2, C2.1, C3.1, C4.1, C5.1, C6.1, C7.1, C8.1, C9.1, C10.1, C11.1, C12.1, C13.1, C14.1, C15.2, D1.-, J1.G1, J1.G2, J1.G3, J1.G4, J2.A1 (GND), J2.A12 (GND), J2.B1 (GND), J2.B12 (GND), J2.P$6, J2.P$7, J2.P$8, J2.P$9, K1.1, K2.1, K3.1, K4.1, K5.3, K5.5, K5.6, K5.7, K5.8, P1.P$1, P6.P$1, P13.P$1, P35.P$1, P44.P$1, Q9.2 (S), Q10.2 (S), R1.1, R4.2, R11.2, R12.1, R14.1, U1.1 (GND), U2.2 (GND), U3.1 (GND1), U3.40 (GND2), U3.41 (GND3), U3.42 (GND4), U3.43 (GND5), U3.44 (GND6), U3.45 (GND7), U3.46 (GND8), U3.47 (GND9), U3.48 (GND10), U3.49 (GND11), U4.25, U4.26, U5.7, U5.8, U5.9, U5.10, U6.2 (GND)
IO1_EXIT: K4.2, R28.1, U3.39 (IO1)
IO2_MENU: K3.2, R27.1, U3.38 (IO2)
IO3: P28.P$1, U3.15 (IO3), U5.1
IO4_DOWN: K5.1, R30.1, U3.4 (IO4)
IO5_CONF: K5.4, R31.2, U3.5 (IO5)
IO6_UP: K5.2, R29.1, U3.6 (IO6)
IO7_LCD_3.3_CTL: R172.1, U3.7 (IO7)
IO8: P20.P$1, U3.12 (IO8), U5.20
IO9: P29.P$1, U3.17 (IO9), U5.2
IO10_SPI_CS: J1.2 (CS), P8.P$1, R20.1, U3.18 (IO10)
IO11_SPI_MOSI: P55.P$1, U3.19 (IO11), U4.14 (SDA)
IO12_SPI_CLK: P54.P$1, U3.20 (IO12), U4.13 (SCL)
IO13_SPI_MISO: J1.7 (DO), P11.P$1, R22.1, U3.21 (IO13)
IO14: P21.P$1, U3.22 (IO14), U5.19
IO15: P30.P$1, U3.8 (IO15), U5.3
IO16: P22.P$1, U3.9 (IO16), U5.18
IO17: P31.P$1, U3.10 (IO17), U5.4
IO18: P23.P$1, U3.11 (IO18), U5.17
IO19: P32.P$1, U3.13 (IO19), U5.5
IO20: P24.P$1, U3.14 (IO20), U5.16
IO21: P33.P$1, U3.23 (IO21), U5.6
IO38: P25.P$1, U3.31 (IO38), U5.15
IO39_SPI_CLK: J1.5 (SCLK), P10.P$1, U3.32 (IO39)
IO40_SPI_MOSI: J1.3 (DI), P9.P$1, R21.1, U3.33 (IO40)
IO41_LED: R16.1, U3.34 (IO41)
IO42_TF_3.3_CTL: R15.1, U3.35 (IO42)
IO45_CS: P53.P$1, U3.26 (IO45), U4.12 (CS)
IO46_D/C: P52.P$1, U3.16 (IO46), U4.11 (D/C)
IO47_RES: P51.P$1, U3.24 (IO47), U4.10 (RES)
IO48_BUSY: P50.P$1, U3.25 (IO48), U4.9 (BUSY)
LCD_GND: C20.1, C22.1, C23.2, C24.2, C25.2, C26.2, C27.2, C28.2, C29.1, D5.C, P42.P$1, P43.P$1, Q9.3 (D), R18.1, R24.1, U4.8 (BS), U4.17 (VSS)
unnamed: Q1.1 (B), R7.2
unnamed: R5.2, U1.2 (TXD)
unnamed: R6.2, U1.3 (RXD)
unnamed: Q2.1 (B), R8.2
unnamed: J2.A5 (CC1), R1.2
unnamed: Q3.1 (G), R10.2, R11.1
unnamed: Q9.1 (G), R172.2
unnamed: Q10.1 (G), R15.2
unnamed: R13.1, R14.2, U2.5 (FB)
unnamed: J1.1 (DATA2), R19.1
unnamed: L1.1, U2.3 (SW)
unnamed: J2.B5 (CC2), R4.1
unnamed: C15.1, U1.4 (V3)
unnamed: R12.2, U6.5 (PROG)
unnamed: R25.1, U4.6 (TSCL)
unnamed: R26.1, U4.7 (TSDA)
unnamed: J1.8 (DATA1), R23.1
unnamed: D1.+, R16.2, R17.2
unnamed: C21.1, D4.C, D5.A
unnamed: C21.2, D6.A, L2.2, Q4.3 (D)
PREVGH: C29.2, D6.C, P56.P$1, U4.21 (PREVGH)
PREVGL: C20.2, D4.A, P57.P$1, U4.23 (PREVGL)
RESE: P37.P$1, Q4.2 (S), R24.2, U4.3 (RESE)
RTS: Q1.2 (E), R8.1, U1.14 (RTS#)
TF_GND: C17.1, C18.1, C19.1, J1.6 (VSS), P45.P$1, Q10.3 (D)
USB_D+: P4.P$1, R3.2, U1.5 (UD+)
USB_D-: P3.P$1, R2.2, U1.6 (UD-)
VBUS: C1.1, C3.2, C4.2, D2.1 (+), J2.A4 (VBUS), J2.A9 (VBUS), J2.B4 (VBUS), J2.B9 (VBUS), P2.P$1, R10.1, R34.2, R35.2, U1.16 (VCC), U6.4 (VCC)
VCOM: C28.1, P62.P$1, U4.24 (VCOM)
VDD: C25.1, P49.P$1, U4.18 (VDD)
VDHR: C23.1, P58.P$1, U4.5 (VDHR)
VIN: C7.2, C8.2, D2.2 (-), D3.C, Q3.2 (S), U2.1 (EN), U2.4 (VIN)
VSH: C26.1, P60.P$1, U4.20 (VSH)
VSL: C27.1, P61.P$1, U4.22 (VSL)

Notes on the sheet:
USB type-c socket
USB to serial port
POWER LED
EXIT button MENU button
ESP32-S3-WROOM-1-N8R8
GPIO Pins
EPD Interface
TF Card
rotate switch
SYS 3.3V Power
Battery
BOOT
RESET
Serial port level conversion
Enable TF / LCD

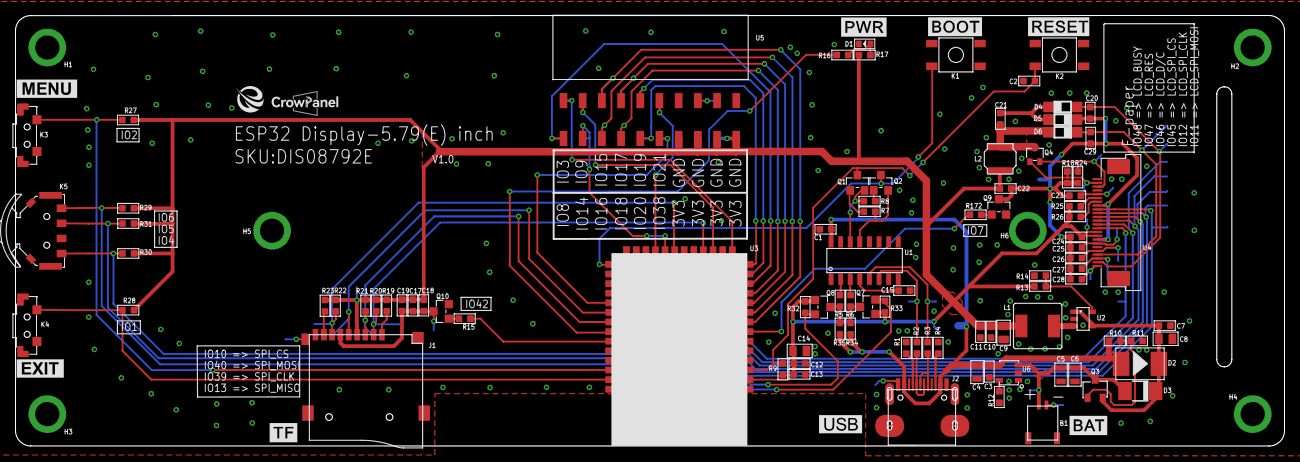
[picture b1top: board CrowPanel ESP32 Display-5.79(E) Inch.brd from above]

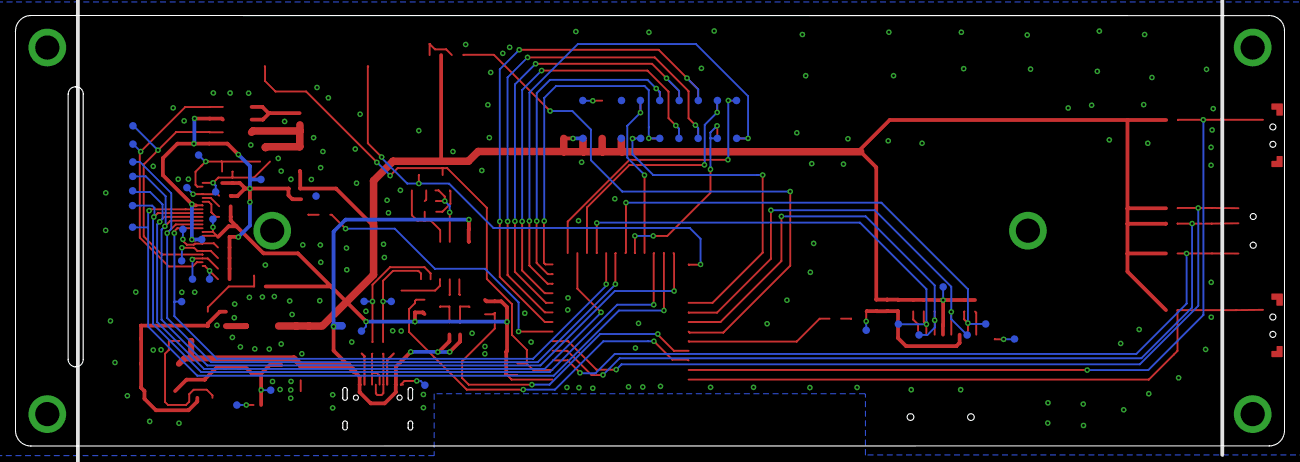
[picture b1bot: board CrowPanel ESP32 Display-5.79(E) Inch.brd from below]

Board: 2 copper layers, 167.9 x 57.0 mm, 145 parts (49 on the bottom side), 78 nets.

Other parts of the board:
U$30: LOGO-1
U$41: LOGO-MIN
